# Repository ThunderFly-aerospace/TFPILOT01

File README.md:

# Teensy 4.1 - Based Flight-Controller for dRehmFlight

This project is a hardware controller board designed specifically for use with the [dRehmFlight open-source flight controller firmware](https://github.com/nickrehm/dRehmFlight). It is based on the Teensy 4.1 microcontroller and provides all the essential interfaces and components needed for a compact, capable flight control unit.

## Features

### Core Components

* **Teensy 4.1** (MIMXRT1062DVJ6B – Arm Cortex-M7 @ 600 MHz)
* **MKL02Z32VFG4** bootloader MCU (required for Teensy compatibility)
* **W25Q64JVXGIM** 8 Mb SPI Flash memory

### Sensors

* **GY-91 (MPU9250 + BMP280)** IMU module connected via **SPI** for reduced latency.

  * Replaces the GY-521 module (MPU6050) commonly used in the default dRehmFlight configuration
  * Integrated magnetometer (AK8963) provides full 9‑DOF capability
  * Integrated BMP280 barometric sensor for altitude estimation

### Storage

* **microSD card slot** for onboard data logging

### Power and Connectivity

* **XT30 power connector** for powering both the autopilot and connected servos
* **PWM outputs** using standard RC servo connectors for direct model integration
* **Multiple high-current GPIO outputs** with transistor drivers for heating control, triggering pyrotechnic or other one-shot actuators
* **USB‑C connector** for power and debug interface (compatible with PJRC Teensy bootloader)

### Expansion and Debugging

* **2.54 mm pin header** for access to I/O pins (except D41)
* **JTAG pins** broken out (not yet tested)

## Acknowledgements

This updated board builds upon the original Teensy 4.1 KiCad example design, transforming it into a purpose-built flight controller platform optimized for dRehmFlight. It adds robust sensing, storage, power distribution, and actuator control features for experimental UAV and aerospace applications.

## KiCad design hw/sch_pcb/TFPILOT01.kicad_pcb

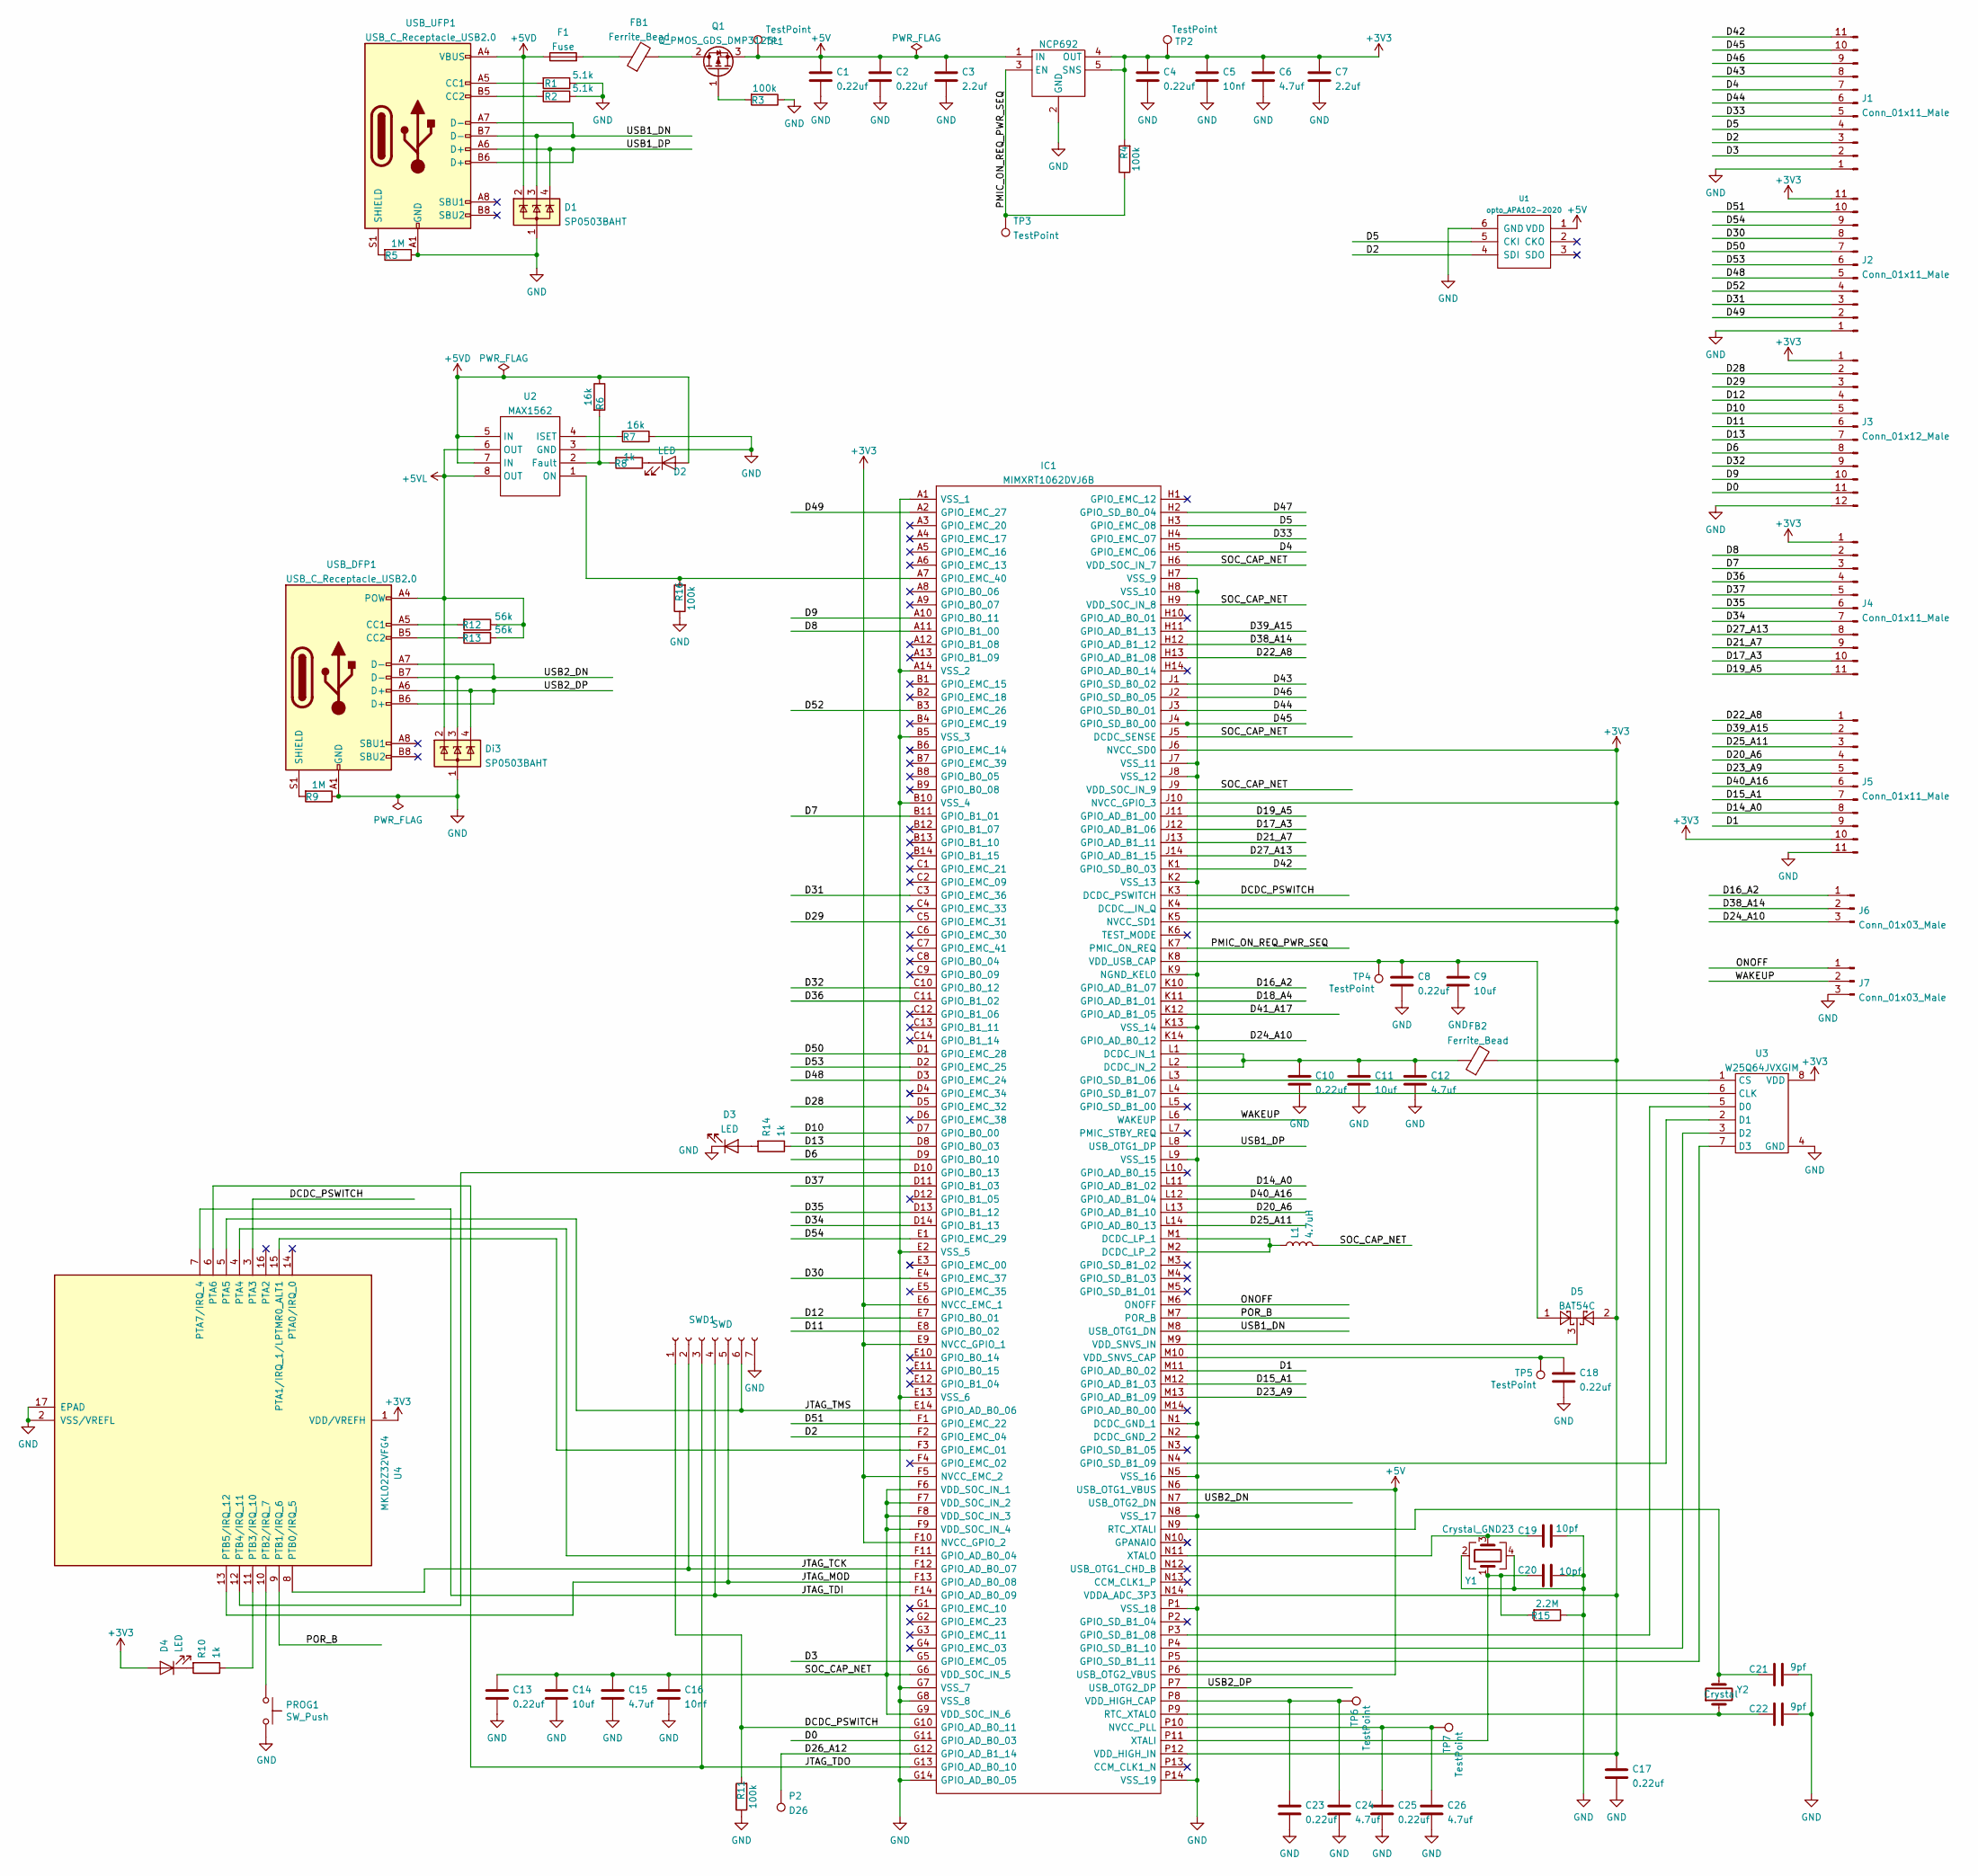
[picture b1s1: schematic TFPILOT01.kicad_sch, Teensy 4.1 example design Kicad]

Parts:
C1, C2, C4, C8, C10, C13, C17, C18, C23, C25: 0.22uf; C_0603_1608Metric; MPN CC0603KRX7R6BB224
C3, C7: 2.2uf; C_0603_1608Metric; MPN CL10B225KP8NNNC
C5, C16: 10nf; C_0603_1608Metric; MPN 0603B103K160CT
C6, C12, C15, C24, C26: 4.7uf; C_0603_1608Metric; MPN CL10B475KQ8NQNC
C9, C11, C14: 10uf; C_0805_2012Metric; MPN GRM21BR71A106KA73K
C19, C20: 10pf; C_0603_1608Metric; MPN CC0603KRNPO9BN100
C21, C22: 9pf; C_0603_1608Metric; MPN GRM1885C1H9R0DA01D
D1: SP0503BAHT; SOT-143
D2, D3, D4: LED; LED_0402_1005Metric
D5: BAT54C; SOT-23
Di3: SP0503BAHT; SOT-143
F1: Fuse; R_0805_2012Metric; MPN 0ZCK0050FF2E
FB1, FB2: Ferrite_Bead; R_0805_2012Metric; MPN FBMH2012HM121-T‎
IC1: MIMXRT1062DVJ6B; BGA196C80P14X14_1200X1200X152; Mouser Part Number 771-MIMXRT1062DVJ6B
J1, J2, J4, J5: Conn_01x11_Male; PinHeader_1x11_P2.54mm_Vertical
J3: Conn_01x12_Male; PinHeader_1x12_P2.54mm_Vertical
J6, J7: Conn_01x03_Male; PinHeader_1x03_P2.54mm_Vertical
L1: 4.7uH; C_0805_2012Metric; MPN LQM21PN4R7MGRD
NCP692: OnSemi NCP692, fixed version; DFN-6-1EP_3x3mm_P0.95mm_EP1.7x2.6mm; MPN NCP692MN33T2G
P2: D26; PinHeader_1x01_P1.00mm_Vertical
PROG1: SW_Push; KMR241GLFS; MPN KMR241GLFS
Q1: Q_PMOS_GDS_DMP3125L; SOT-23
R1, R2: 5.1k; R_0603_1608Metric; MPN RC0603FR-075K1L
R3, R4, R11, R16: 100k; R_0603_1608Metric
R5, R9: 1M; R_0603_1608Metric
R6, R7: 16k; R_0603_1608Metric
R8, R10, R14: 1k; R_0402_1005Metric
R12, R13: 56k; R_0603_1608Metric; MPN RMCF0603FT56K0
R15: 2.2M; R_0603_1608Metric
SWD1: SWD; PinHeader_1x07_P1.27mm_Vertical
TP1, TP2, TP3, TP4, TP5, TP6, TP7: TestPoint; TestPoint_Pad_D1.0mm
U1: opto_APA102-2020; APA102-2020
U2: MAX1562; SO-8_3.9x4.9mm_P1.27mm
U3: W25Q64JVXGIM; XSON8_4x4mm
U4: MKL02Z32VFG4; QFN-16-1EP_3x3mm_P0.5mm_EP1.8x1.8mm; MPN Custom firmware part
USB_DFP1: USB_C_Receptacle_USB2.0; TYPE-C-31-M-14
USB_UFP1: USB_C_Receptacle_USB2.0; TYPE-C-31-M-14
Y1: Crystal_GND23; Crystal_SMD_Abracon_ABM3B-4Pin_5.0x3.2mm
Y2: Crystal; Crystal_SMD_2012-2Pin_2.0x1.2mm; MPN ABS06-32.768KHZ-9-1-T

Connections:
+3V3: C4.1, C5.1, C6.1, C7.1, C17.1, D4.2 (A), D5.2, FB2.2, IC1.E6 (NVCC_EMC_1), IC1.E9 (NVCC_GPIO_1), IC1.F5 (NVCC_EMC_2), IC1.F10 (NVCC_GPIO_2), IC1.J6 (NVCC_SD0), IC1.J10 (NVCC_GPIO_3), IC1.K4 (DCDC__IN_Q), IC1.K5 (NVCC_SD1), IC1.N14 (VDDA_ADC_3P3), IC1.P12 (VDD_HIGH_IN), J2.11, J3.1, J4.1, J5.10, NCP692.4 (OUT), NCP692.5 (SNS), R4.2, TP2.1, U3.8 (VDD), U4.1 (VDD/VREFH)
+5V: C1.1, C2.1, C3.1, IC1.N6 (USB_OTG1_VBUS), IC1.P6 (USB_OTG2_VBUS), NCP692.1 (IN), NCP692.6 (IN), Q1.3 (S), TP1.1, U1.1 (VDD)
+5VD: D1.2 (K), D2.2 (A), F1.1, R6.1, U2.5 (IN), U2.7 (IN), USB_UFP1.A4 (VBUS), USB_UFP1.A9 (VBUS), USB_UFP1.B4 (VBUS), USB_UFP1.B9 (VBUS)
+5VL: Di3.2 (K), R12.1, R13.1, U2.6 (OUT), U2.8 (OUT), USB_DFP1.A4 (POW), USB_DFP1.A9 (POW), USB_DFP1.B4 (POW), USB_DFP1.B9 (POW)
/D0: IC1.G11 (GPIO_AD_B0_03), J3.11
/D1: IC1.M11 (GPIO_AD_B0_02), J5.9
/D2: IC1.F2 (GPIO_EMC_04), J1.3, U1.4 (SDI)
/D3: IC1.G5 (GPIO_EMC_05), J1.2
/D4: IC1.H5 (GPIO_EMC_06), J1.7
/D5: IC1.H3 (GPIO_EMC_08), J1.4, U1.5 (CKI)
/D6: IC1.D9 (GPIO_B0_10), J3.8
/D7: IC1.B11 (GPIO_B1_01), J4.3
/D8: IC1.A11 (GPIO_B1_00), J4.2
/D9: IC1.A10 (GPIO_B0_11), J3.10
/D10: IC1.D7 (GPIO_B0_00), J3.5
/D11: IC1.E8 (GPIO_B0_02), J3.6
/D12: IC1.E7 (GPIO_B0_01), J3.4
/D13: IC1.D8 (GPIO_B0_03), J3.7, R14.1
/D14_A0: IC1.L11 (GPIO_AD_B1_02), J5.8
/D15_A1: IC1.M12 (GPIO_AD_B1_03), J5.7
/D16_A2: IC1.K10 (GPIO_AD_B1_07), J6.1
/D17_A3: IC1.J12 (GPIO_AD_B1_06), J4.10
/D18_A4: IC1.K11 (GPIO_AD_B1_01)
/D19_A5: IC1.J11 (GPIO_AD_B1_00), J4.11
/D20_A6: IC1.L13 (GPIO_AD_B1_10), J5.4
/D21_A7: IC1.J13 (GPIO_AD_B1_11), J4.9
/D22_A8: IC1.H13 (GPIO_AD_B1_08), J5.1
/D23_A9: IC1.M13 (GPIO_AD_B1_09), J5.5
/D24_A10: IC1.K14 (GPIO_AD_B0_12), J6.3
/D25_A11: IC1.L14 (GPIO_AD_B0_13), J5.3
/D26_A12: IC1.G12 (GPIO_AD_B1_14), P2.1
/D27_A13: IC1.J14 (GPIO_AD_B1_15), J4.8
/D28: IC1.D5 (GPIO_EMC_32), J3.2
/D29: IC1.C5 (GPIO_EMC_31), J3.3
/D30: IC1.E4 (GPIO_EMC_37), J2.8
/D31: IC1.C3 (GPIO_EMC_36), J2.3
/D32: IC1.C10 (GPIO_B0_12), J3.9
/D33: IC1.H4 (GPIO_EMC_07), J1.5
/D34: IC1.D14 (GPIO_B1_13), J4.7
/D35: IC1.D13 (GPIO_B1_12), J4.6
/D36: IC1.C11 (GPIO_B1_02), J4.4
/D37: IC1.D11 (GPIO_B1_03), J4.5
/D38_A14: IC1.H12 (GPIO_AD_B1_12), J6.2
/D39_A15: IC1.H11 (GPIO_AD_B1_13), J5.2
/D40_A16: IC1.L12 (GPIO_AD_B1_04), J5.6
/D41_A17: IC1.K12 (GPIO_AD_B1_05)
/D42: IC1.K1 (GPIO_SD_B0_03), J1.11
/D43: IC1.J1 (GPIO_SD_B0_02), J1.8
/D44: IC1.J3 (GPIO_SD_B0_01), J1.6
/D45: IC1.J4 (GPIO_SD_B0_00), J1.10
/D46: IC1.J2 (GPIO_SD_B0_05), J1.9
/D47: IC1.H2 (GPIO_SD_B0_04)
/D48: IC1.D3 (GPIO_EMC_24), J2.5
/D49: IC1.A2 (GPIO_EMC_27), J2.2
/D50: IC1.D1 (GPIO_EMC_28), J2.7
/D51: IC1.F1 (GPIO_EMC_22), J2.10
/D52: IC1.B3 (GPIO_EMC_26), J2.4
/D53: IC1.D2 (GPIO_EMC_25), J2.6
/D54: IC1.E1 (GPIO_EMC_29), J2.9
/DCDC_PSWITCH: IC1.G10 (GPIO_AD_B0_11), IC1.K3 (DCDC_PSWITCH), R11.2, SWD1.1, U4.3 (PTA3)
/JTAG_MOD: IC1.F13 (GPIO_AD_B0_08), SWD1.5, U4.13 (PTB5/IRQ_12)
/JTAG_TCK: IC1.F12 (GPIO_AD_B0_07), SWD1.2, U4.8 (PTB0/IRQ_5)
/JTAG_TDI: IC1.F14 (GPIO_AD_B0_09), SWD1.4, U4.7 (PTA7/IRQ_4)
/JTAG_TDO: IC1.G13 (GPIO_AD_B0_10), SWD1.3, U4.6 (PTA6)
/JTAG_TMS: IC1.E14 (GPIO_AD_B0_06), SWD1.6, U4.5 (PTA5)
/ONOFF: IC1.M6 (ONOFF), J7.1
/PMIC_ON_REQ_PWR_SEQ: IC1.K7 (PMIC_ON_REQ), NCP692.3 (EN), R4.1, TP3.1
/POR_B: IC1.M7 (POR_B), U4.9 (PTB1/IRQ_6)
/SOC_CAP_NET: C13.1, C14.1, C15.1, C16.1, IC1.F6 (VDD_SOC_IN_1), IC1.F7 (VDD_SOC_IN_2), IC1.F8 (VDD_SOC_IN_3), IC1.F9 (VDD_SOC_IN_4), IC1.G6 (VDD_SOC_IN_5), IC1.G9 (VDD_SOC_IN_6), IC1.H6 (VDD_SOC_IN_7), IC1.H9 (VDD_SOC_IN_8), IC1.J5 (DCDC_SENSE), IC1.J9 (VDD_SOC_IN_9), L1.2
/USB1_DN: D1.3 (K), IC1.M8 (USB_OTG1_DN), USB_UFP1.A7 (D-), USB_UFP1.B7 (D-)
/USB1_DP: D1.4 (K), IC1.L8 (USB_OTG1_DP), USB_UFP1.A6 (D+), USB_UFP1.B6 (D+)
/USB2_DN: Di3.3 (K), IC1.N7 (USB_OTG2_DN), USB_DFP1.A7 (D-), USB_DFP1.B7 (D-)
/USB2_DP: Di3.4 (K), IC1.P7 (USB_OTG2_DP), USB_DFP1.A6 (D+), USB_DFP1.B6 (D+)
/WAKEUP: IC1.L6 (WAKEUP), J7.2
GND: C1.2, C2.2, C3.2, C4.2, C5.2, C6.2, C7.2, C8.2, C9.2, C10.2, C11.2, C12.2, C13.2, C14.2, C15.2, C16.2, C17.2, C18.2, C19.2, C20.2, C21.2, C22.2, C23.2, C24.2, C25.2, C26.2, D1.1 (A), D3.1 (K), Di3.1 (A), IC1.A1 (VSS_1), IC1.A14 (VSS_2), IC1.B5 (VSS_3), IC1.B10 (VSS_4), IC1.E2 (VSS_5), IC1.E13 (VSS_6), IC1.G7 (VSS_7), IC1.G8 (VSS_8), IC1.G14 (GPIO_AD_B0_05), IC1.H7 (VSS_9), IC1.H8 (VSS_10), IC1.J7 (VSS_11), IC1.J8 (VSS_12), IC1.K2 (VSS_13), IC1.K9 (NGND_KEL0), IC1.K13 (VSS_14), IC1.L9 (VSS_15), IC1.N1 (DCDC_GND_1), IC1.N2 (DCDC_GND_2), IC1.N5 (VSS_16), IC1.N8 (VSS_17), IC1.P1 (VSS_18), IC1.P14 (VSS_19), J1.1, J2.1, J3.12, J5.11, J7.3, NCP692.2 (GND), NCP692.7 (GND), PROG1.2, R1.1, R2.1, R3.1, R5.1, R7.1, R9.1, R11.1, R15.1, R16.1, SWD1.7, U1.6 (GND), U2.3 (GND), U3.4 (GND), U4.2 (VSS/VREFL), U4.17 (EPAD), USB_DFP1.A1 (GND), USB_DFP1.A12 (GND), USB_DFP1.B1 (GND), USB_DFP1.B12 (GND), USB_UFP1.A1 (GND), USB_UFP1.A12 (GND), USB_UFP1.B1 (GND), USB_UFP1.B12 (GND), Y1.2, Y1.4
unnamed: D2.1 (K), R8.1
unnamed: D3.2 (A), R14.2
unnamed: D4.1 (K), R10.2
unnamed: F1.2, FB1.1
unnamed: C10.1, C11.1, C12.1, FB2.1, IC1.L1 (DCDC_IN_1), IC1.L2 (DCDC_IN_2)
unnamed: IC1.M1 (DCDC_LP_1), IC1.M2 (DCDC_LP_2), L1.1
unnamed: IC1.F11 (GPIO_AD_B0_04), U4.4 (PTA4)
unnamed: IC1.D10 (GPIO_B0_13), U4.12 (PTB4/IRQ_11)
unnamed: IC1.F3 (GPIO_EMC_01), U4.15 (PTA1/IRQ_1/LPTMR0_ALT1)
unnamed: IC1.A7 (GPIO_EMC_40), R16.2, U2.1 (ON)
unnamed: IC1.L3 (GPIO_SD_B1_06), U3.1 (CS)
unnamed: IC1.L4 (GPIO_SD_B1_07), U3.6 (CLK)
unnamed: IC1.P3 (GPIO_SD_B1_08), U3.5 (D0)
unnamed: IC1.N4 (GPIO_SD_B1_09), U3.2 (D1)
unnamed: IC1.P4 (GPIO_SD_B1_10), U3.3 (D2)
unnamed: IC1.P5 (GPIO_SD_B1_11), U3.7 (D3)
unnamed: C25.1, C26.1, IC1.P10 (NVCC_PLL), TP7.1
unnamed: C21.1, IC1.N9 (RTC_XTALI), Y2.2
unnamed: C22.1, IC1.P9 (RTC_XTALO), Y2.1
unnamed: C23.1, C24.1, IC1.P8 (VDD_HIGH_CAP), TP6.1
unnamed: C18.1, IC1.M10 (VDD_SNVS_CAP), TP5.1
unnamed: D5.3, IC1.M9 (VDD_SNVS_IN)
unnamed: C8.1, C9.1, D5.1, IC1.K8 (VDD_USB_CAP), TP4.1
unnamed: C20.1, IC1.P11 (XTALI), R15.2, Y1.1
unnamed: C19.1, IC1.N11 (XTALO), Y1.3
unnamed: FB1.2, Q1.2 (D)
unnamed: Q1.1 (G), R3.2
unnamed: R6.2, R8.2, U2.2 (Fault)
unnamed: R7.2, U2.4 (ISET)
unnamed: PROG1.1, U4.10 (PTB2/IRQ_7)
unnamed: R10.1, U4.11 (PTB3/IRQ_10)
unnamed: R12.2, USB_DFP1.A5 (CC1)
unnamed: R13.2, USB_DFP1.B5 (CC2)
unnamed: R9.2, USB_DFP1.S1 (SHIELD)
unnamed: R1.2, USB_UFP1.A5 (CC1)
unnamed: R2.2, USB_UFP1.B5 (CC2)
unnamed: R5.2, USB_UFP1.S1 (SHIELD)

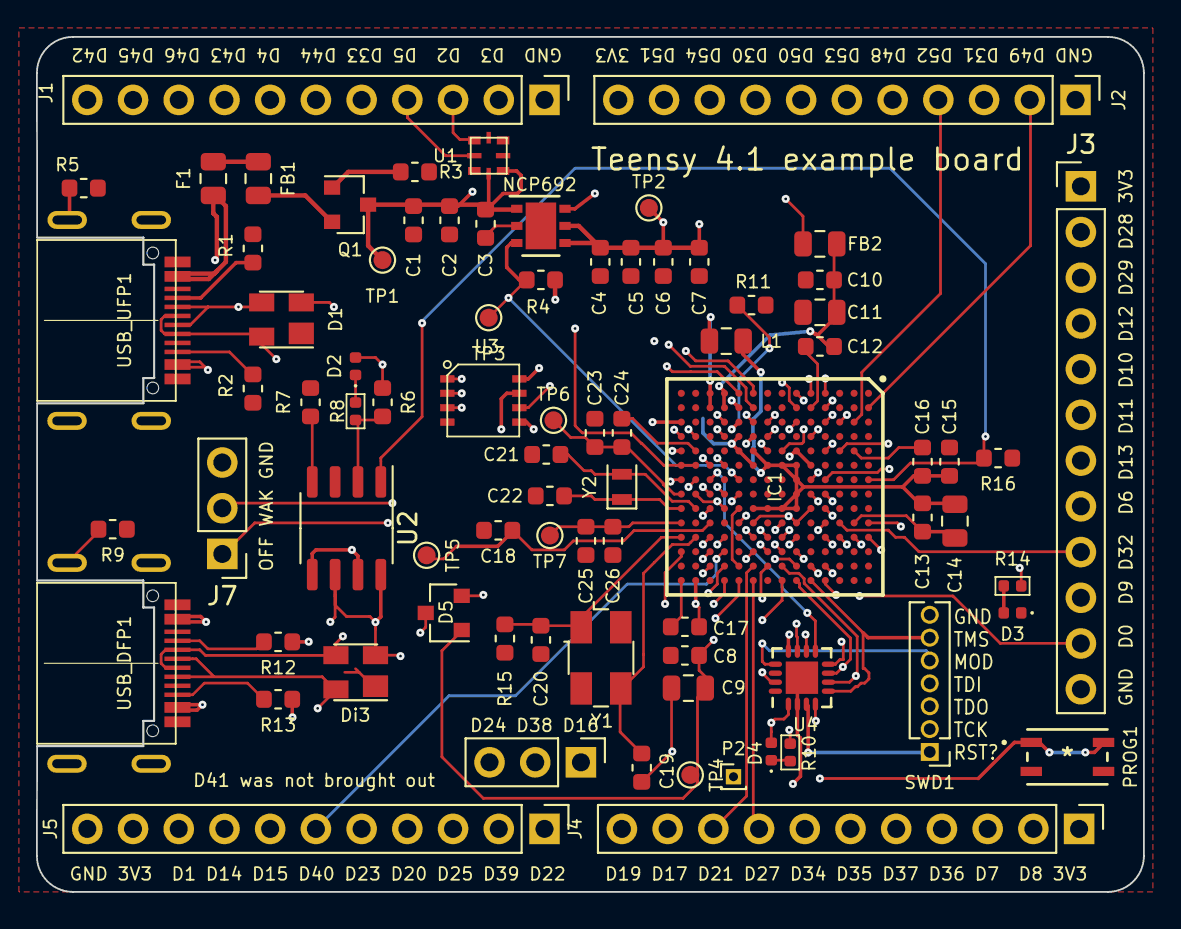
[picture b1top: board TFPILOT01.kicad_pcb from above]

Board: 4 copper layers, 61.5 x 47.5 mm, 80 parts (0 on the bottom side), 109 nets.

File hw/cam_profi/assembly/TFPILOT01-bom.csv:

Component,Description,Part,References,Value,Footprint,Quantity Per PCB,Datasheet,mfgr,mpn,height,mouser part number,mouser price/stock,manufacturer_name,manufacturer_part_number
1,Unpolarized capacitor,C,C21C22,9pf,C_0603_1608Metric,2,~,Jellybean (X7R or better),GRM1885C1H9R0DA01D,,,,,
2,Unpolarized capacitor,C,C19C20,10pf,C_0603_1608Metric,2,~,Jellybean (X7R or better),CC0603KRNPO9BN100,,,,,
3,Unpolarized capacitor,C,C5C16,10nf,C_0603_1608Metric,2,~,Jellybean (X7R or better),0603B103K160CT,,,,,
4,Unpolarized capacitor,C,C1C2C4C8C10C13C17C18C23C25,0.22uf,C_0603_1608Metric,10,~,Jellybean (X7R or better),CC0603KRX7R6BB224,,,,,
5,Unpolarized capacitor,C,C3C7,2.2uf,C_0603_1608Metric,2,~,Jellybean (X7R or better),CL10B225KP8NNNC,,,,,
6,Unpolarized capacitor,C,C6C12C15C24C26,4.7uf,C_0603_1608Metric,5,~,Jellybean (X7R or better),CL10B475KQ8NQNC,,,,,
7,Unpolarized capacitor,C,C9C11C14,10uf,C_0805_2012Metric,3,~,Jellybean (X7R or better),GRM21BR71A106KA73K,,,,,
8,"dual schottky barrier diode, common cathode",BAT54C,D5,BAT54C,SOT-23,1,http://www.diodes.com/_files/datasheets/ds11005.pdf,,,,,,,
9,Light emitting diode,LED,D2D3D4,LED,LED_0402_1005Metric,3,~,,,,,,,
10,"TVS Diode Array, 5.5V Standoff, 3 Channels, SOT-143 package",SP0503BAHT,D1Di3,SP0503BAHT,SOT-143,2,http://www.littelfuse.com/~/media/files/littelfuse/technical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,,,,,,,
11,Fuse,Fuse,F1,Fuse,R_0805_2012Metric,1,~,Bel Fuse Inc,0ZCK0050FF2E,,,,,
12,Ferrite bead,Ferrite_Bead,FB1FB2,Ferrite_Bead,R_0805_2012Metric,2,~,Taiyo Yuden,FBMH2012HM121-T‎,,,,,
13,IC MCU 32BIT EXT MEM 196MAPBGA,MIMXRT1062DVJ6B,IC1,MIMXRT1062DVJ6B,BGA196C80P14X14_1200X1200X152,1,https://www.nxp.com/docs/en/nxp/data-sheets/IMXRT1060CEC.pdf,,,1.52,771-MIMXRT1062DVJ6B,https://www.mouser.co.uk/ProductDetail/NXP-Semiconductors/MI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,NXP,MIMXRT1062DVJ6B
14,"Generic connector, single row, 01x03, script generated (kicad-library-utils/schlib/autogen/connector/)",Conn_01x03_Male,J6J7,Conn_01x03_Male,PinHeader_1x03_P2.54mm_Vertical,2,~,,,,,,,
15,"Generic connector, single row, 01x11, script generated (kicad-library-utils/schlib/autogen/connector/)",Conn_01x11_Male,J1J2J4J5,Conn_01x11_Male,PinHeader_1x11_P2.54mm_Vertical,4,~,,,,,,,
16,"Generic connector, single row, 01x12, script generated (kicad-library-utils/schlib/autogen/connector/)",Conn_01x12_Male,J3,Conn_01x12_Male,PinHeader_1x12_P2.54mm_Vertical,1,~,,,,,,,
17,Inductor,L,L1,4.7uH,C_0805_2012Metric,1,~,,LQM21PN4R7MGRD,,,,,
18,"3x3mm LDO, 1A","OnSemi NCP692, fixed version",NCP692,"OnSemi NCP692, fixed version",DFN-6-1EP_3x3mm_P0.95mm_EP1.7x2.6mm,1,https://www.onsemi.com/pdf/datasheet/ncp690-d.pdf,Onsemi,NCP692MN33T2G,,,,,
19,"Push button switch, generic, two pins",SW_Push,PROG1,SW_Push,KMR241GLFS,1,,C&K,KMR241GLFS,,,,,
20,"P-MOSFET transistor, gate/drain/source",Q_PMOS_GDS,Q1,Q_PMOS_GDS_DMP3125L,SOT-23,1,https://www.diodes.com/assets/Datasheets/DMP3125L.pdf,,,,,,,
21,Resistor,R,R8R10R14,1k,R_0402_1005Metric,3,~,,,,,,,
22,Resistor,R,R1R2,5.1k,R_0603_1608Metric,2,~,Jellybean,RC0603FR-075K1L,,,,,
23,Resistor,R,R6R7,16k,R_0603_1608Metric,2,~,Jellybean,,,,,,
24,Resistor,R,R12R13,56k,R_0603_1608Metric,2,~,Jellybean,RMCF0603FT56K0,,,,,
25,Resistor,R,R3R4R11R16,100k,R_0603_1608Metric,4,~,,,,,,,
26,Resistor,R,R5R9,1M,R_0603_1608Metric,2,~,,,,,,,
27,Resistor,R,R15,2.2M,R_0603_1608Metric,1,~,,,,,,,
28,"Generic connector, single row, 01x07, script generated (kicad-library-utils/schlib/autogen/connector/)",Conn_01x07_Female,SWD1,SWD,PinHeader_1x07_P1.27mm_Vertical,1,~,,,,,,,
29,"MAX1562ESA, USB power switch 4A, Current-Limited Switches with Autoreset and Fault Blanking",MAX1562,U2,MAX1562,SO-8_3.9x4.9mm_P1.27mm,1,,,,,,,,
30,"Kinetis KL02 series, 48-MHz/32-bit ARM Cortex-M0+, 32 kB flash, 4 kB SRAM, QFN-16",MKL02Z32VFG4,U4,MKL02Z32VFG4,QFN-16-1EP_3x3mm_P0.5mm_EP1.8x1.8mm,1,http://www.nxp.com/docs/en/data-sheet/KL02P32M48SF0.pdf,Supplied by Roest Coffee,Custom firmware part,,,,,
31,"Flash chip for T4.1 designs, XSON-8 package,  W25Q64JVXGIM TR, NOR Flash spiFlash, 64M-bit, DTR, 4Kb Uniform Sector",W25Q64VXGIM,U3,W25Q64JVXGIM,XSON8_4x4mm,1,,,,,,,,
32,,opto_APA102-2020,U1,opto_APA102-2020,APA102-2020,1,,,,,,,,
33,USB 2.0-only Type-C Receptacle connector that does not connect to VBUS automatically,USB_C_Receptacle_USB2.0_NOPOW,USB_DFP1,USB_C_Receptacle_USB2.0,TYPE-C-31-M-14,1,https://www.usb.org/sites/default/files/documents/usb_type-c.zip,,,,,,,
34,USB 2.0-only Type-C Receptacle connector,USB_C_Receptacle_USB2.0,USB_UFP1,USB_C_Receptacle_USB2.0,TYPE-C-31-M-14,1,https://www.usb.org/sites/default/files/documents/usb_type-c.zip,,,,,,,
35,Two pin crystal,Crystal,Y2,Crystal,Crystal_SMD_2012-2Pin_2.0x1.2mm,1,~,Abracon,ABS06-32.768KHZ-9-1-T,,,,,
36,"Four pin crystal, GND on pins 2 and 4",Crystal_GND24,Y1,Crystal_GND23,Crystal_SMD_Abracon_ABM3B-4Pin_5.0x3.2mm,1,~,,,,,,,

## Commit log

2025-10-04 Modify repository structure. Cleanup Update project to KiCADv9. Activate workflows.
2025-10-04 Cleanup corrupted subdirectory.
2025-10-04 Add recovered KiCAD 9 project.
2025-10-04 Update actions products
2025-10-04 Remove USB-C host connector.
2025-10-04 Update documentation.
2025-10-05 Update workflow files
2025-10-05 Update README.md
    Add generated images.
2026-02-15 Automatic update of KiCAD outputs

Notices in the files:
parts and their libraries:
Copyright 2016 Accelerated Designs. All rights reserved.
